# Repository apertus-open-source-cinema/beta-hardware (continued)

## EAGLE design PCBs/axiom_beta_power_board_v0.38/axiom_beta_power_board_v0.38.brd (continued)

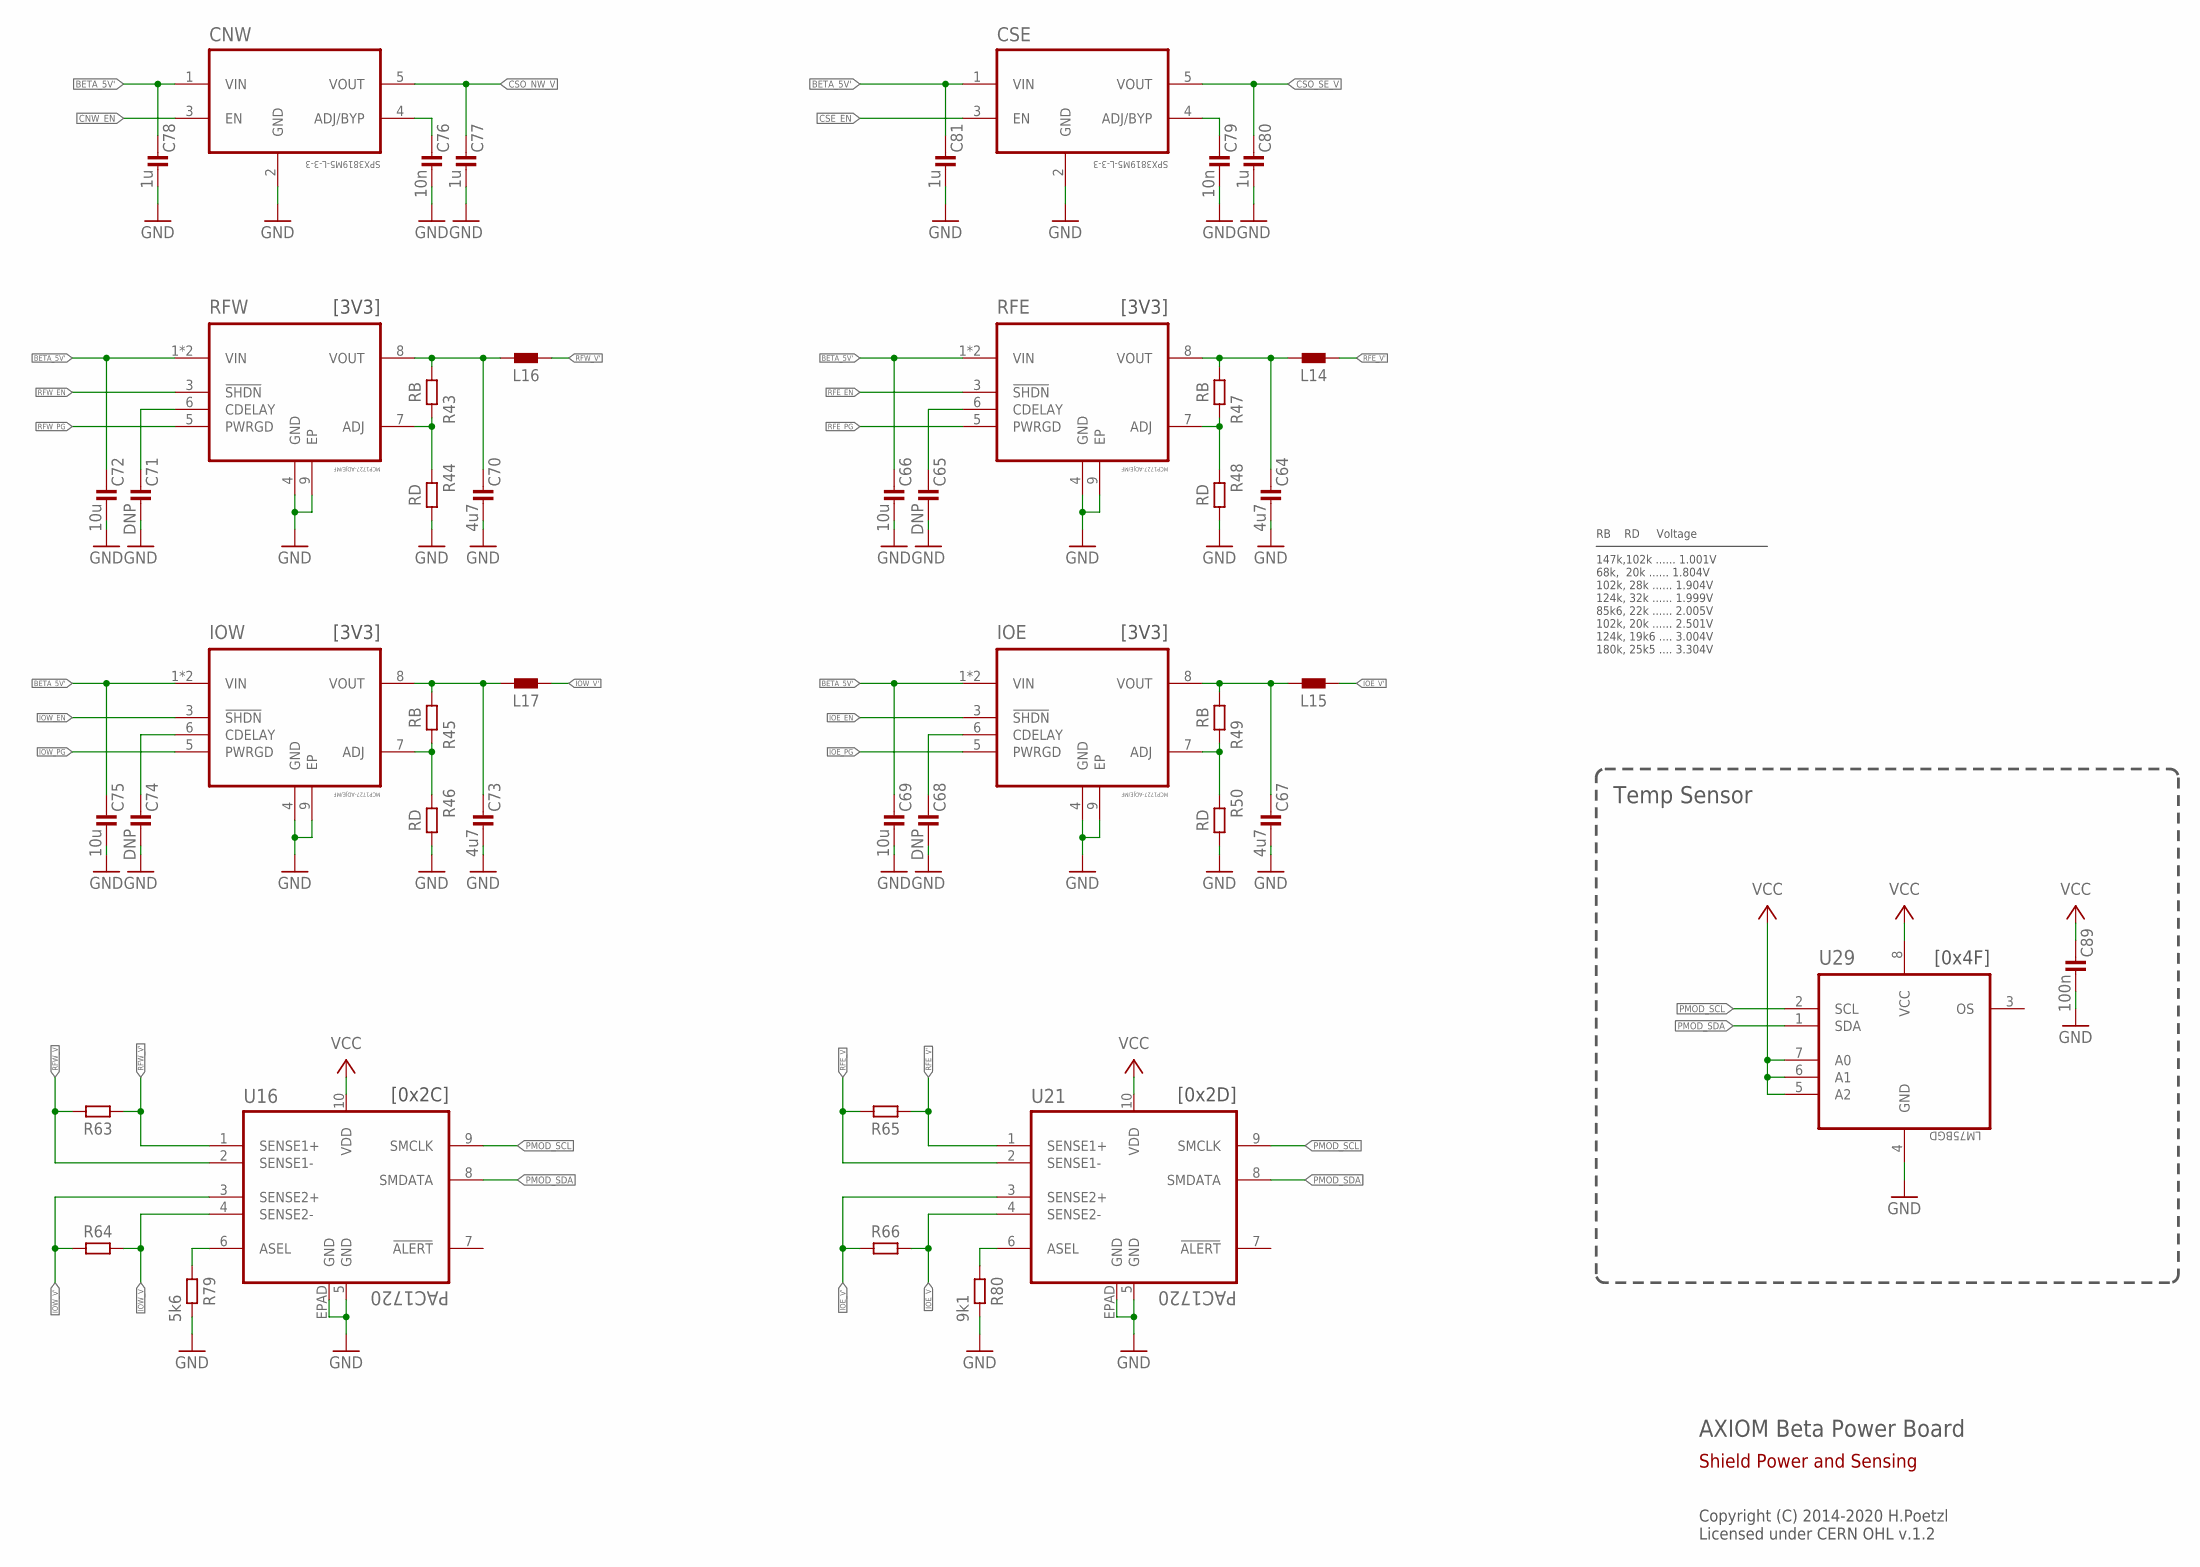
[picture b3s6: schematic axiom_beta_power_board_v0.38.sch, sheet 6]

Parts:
C64, C67, C70, C73: 4u7; 0603-B
C65, C68, C71, C74: DNP; 0402-B
C66, C69, C72, C75: 10u; 0603-B
C76, C79: 10n; 0402-B
C77, C78, C80, C81: 1u; 0402-B
C89: 100n; 0402-B
CNW: SPX3819M5-L-3-3; SOT95P280X145-5N
CSE: SPX3819M5-L-3-3; SOT95P280X145-5N
IOE: MCP1727-ADJE/MF; DFN65P300X300X100-9N
IOW: MCP1727-ADJE/MF; DFN65P300X300X100-9N
L14, L15, L16, L17: L0805-B; 0805-B
R43, R45, R47, R49: RB; 0402-B
R44, R46, R48, R50: RD; 0402-B
R63, R64, R65, R66: R1206-B; 1206-B
R79: 5k6; 0402-B
R80: 9k1; 0402-B
RFE: MCP1727-ADJE/MF; DFN65P300X300X100-9N
RFW: MCP1727-ADJE/MF; DFN65P300X300X100-9N
U16, U21: PAC1720; DFN3X3_10LEAD
U29: LM75BGD; SOT996-2/3

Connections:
BETA_5V': C66.1, C69.1, C72.1, C75.1, C78.1, C81.1, CNW.1 (VIN), CSE.1 (VIN), IOE.1 (VIN), IOE.2 (VIN), IOW.1 (VIN), IOW.2 (VIN), RFE.1 (VIN), RFE.2 (VIN), RFW.1 (VIN), RFW.2 (VIN); also elsewhere on the board
CNW_BYP: C76.1, CNW.4 (ADJ/BYP)
CNW_EN: CNW.3 (EN); also elsewhere on the board
CSE_BYP: C79.1, CSE.4 (ADJ/BYP)
CSE_EN: CSE.3 (EN); also elsewhere on the board
CSO_NW_V: C77.1, CNW.5 (VOUT); also elsewhere on the board
CSO_SE_V: C80.1, CSE.5 (VOUT); also elsewhere on the board
GND: C64.2, C65.2, C66.2, C67.2, C68.2, C69.2, C70.2, C71.2, C72.2, C73.2, C74.2, C75.2, C76.2, C77.2, C78.2, C79.2, C80.2, C81.2, C89.2, CNW.2 (GND), CSE.2 (GND), IOE.4 (GND), IOE.9 (EP), IOW.4 (GND), IOW.9 (EP), R44.2, R46.2, R48.2, R50.2, R79.2, R80.2, RFE.4 (GND), RFE.9 (EP), RFW.4 (GND), RFW.9 (EP), U16.5 (GND), U16.EPAD (GND), U21.5 (GND), U21.EPAD (GND), U29.4 (GND); also elsewhere on the board
IOE_EN: IOE.3 (!SHDN); also elsewhere on the board
IOE_PG: IOE.5 (PWRGD); also elsewhere on the board
IOE_V: R66.2, U21.4 (SENSE2-); also elsewhere on the board
IOE_V': L15.2, R66.1, U21.3 (SENSE2+)
IOW_EN: IOW.3 (!SHDN); also elsewhere on the board
IOW_PG: IOW.5 (PWRGD); also elsewhere on the board
IOW_V: R64.2, U16.4 (SENSE2-); also elsewhere on the board
IOW_V': L17.2, R64.1, U16.3 (SENSE2+)
unnamed: C64.1, L14.1, R47.1, RFE.8 (VOUT)
unnamed: R47.2, R48.1, RFE.7 (ADJ)
unnamed: C65.1, RFE.6 (CDELAY)
unnamed: C67.1, IOE.8 (VOUT), L15.1, R49.1
unnamed: IOE.7 (ADJ), R49.2, R50.1
unnamed: C68.1, IOE.6 (CDELAY)
unnamed: C70.1, L16.1, R43.1, RFW.8 (VOUT)
unnamed: R43.2, R44.1, RFW.7 (ADJ)
unnamed: C71.1, RFW.6 (CDELAY)
unnamed: C73.1, IOW.8 (VOUT), L17.1, R45.1
unnamed: IOW.7 (ADJ), R45.2, R46.1
unnamed: C74.1, IOW.6 (CDELAY)
unnamed: R79.1, U16.6 (ASEL)
unnamed: R80.1, U21.6 (ASEL)
PMOD_SCL: U16.9 (SMCLK), U21.9 (SMCLK), U29.2 (SCL); also elsewhere on the board
PMOD_SDA: U16.8 (SMDATA), U21.8 (SMDATA), U29.1 (SDA); also elsewhere on the board
RFE_EN: RFE.3 (!SHDN); also elsewhere on the board
RFE_PG: RFE.5 (PWRGD); also elsewhere on the board
RFE_V: R65.2, U21.2 (SENSE1-); also elsewhere on the board
RFE_V': L14.2, R65.1, U21.1 (SENSE1+)
RFW_EN: RFW.3 (!SHDN); also elsewhere on the board
RFW_PG: RFW.5 (PWRGD); also elsewhere on the board
RFW_V: R63.2, U16.2 (SENSE1-); also elsewhere on the board
RFW_V': L16.2, R63.1, U16.1 (SENSE1+)
VCC: C89.1, U16.10 (VDD), U21.10 (VDD), U29.5 (A2), U29.6 (A1), U29.7 (A0), U29.8 (VCC); also elsewhere on the board

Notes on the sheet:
AXIOM Beta Power Board
Copyright (C) 2014-2020 H.Poetzl Licensed under CERN OHL v.1.2
Shield Power and Sensing
[0x2C]
[0x2D]
[0x4F]
Temp Sensor
RB RD Voltage 147k,102k ...... 1.001V 68k, 20k ...... 1.804V 102k, 28k ...... 1.904V 124k, 32k ...... 1.999V 85k6, 22k ...... 2.005V 102k, 20k ...... 2.501V 124k, 19k6 .... 3.004V 180k, 25k5 .... 3.304V
[3V3]

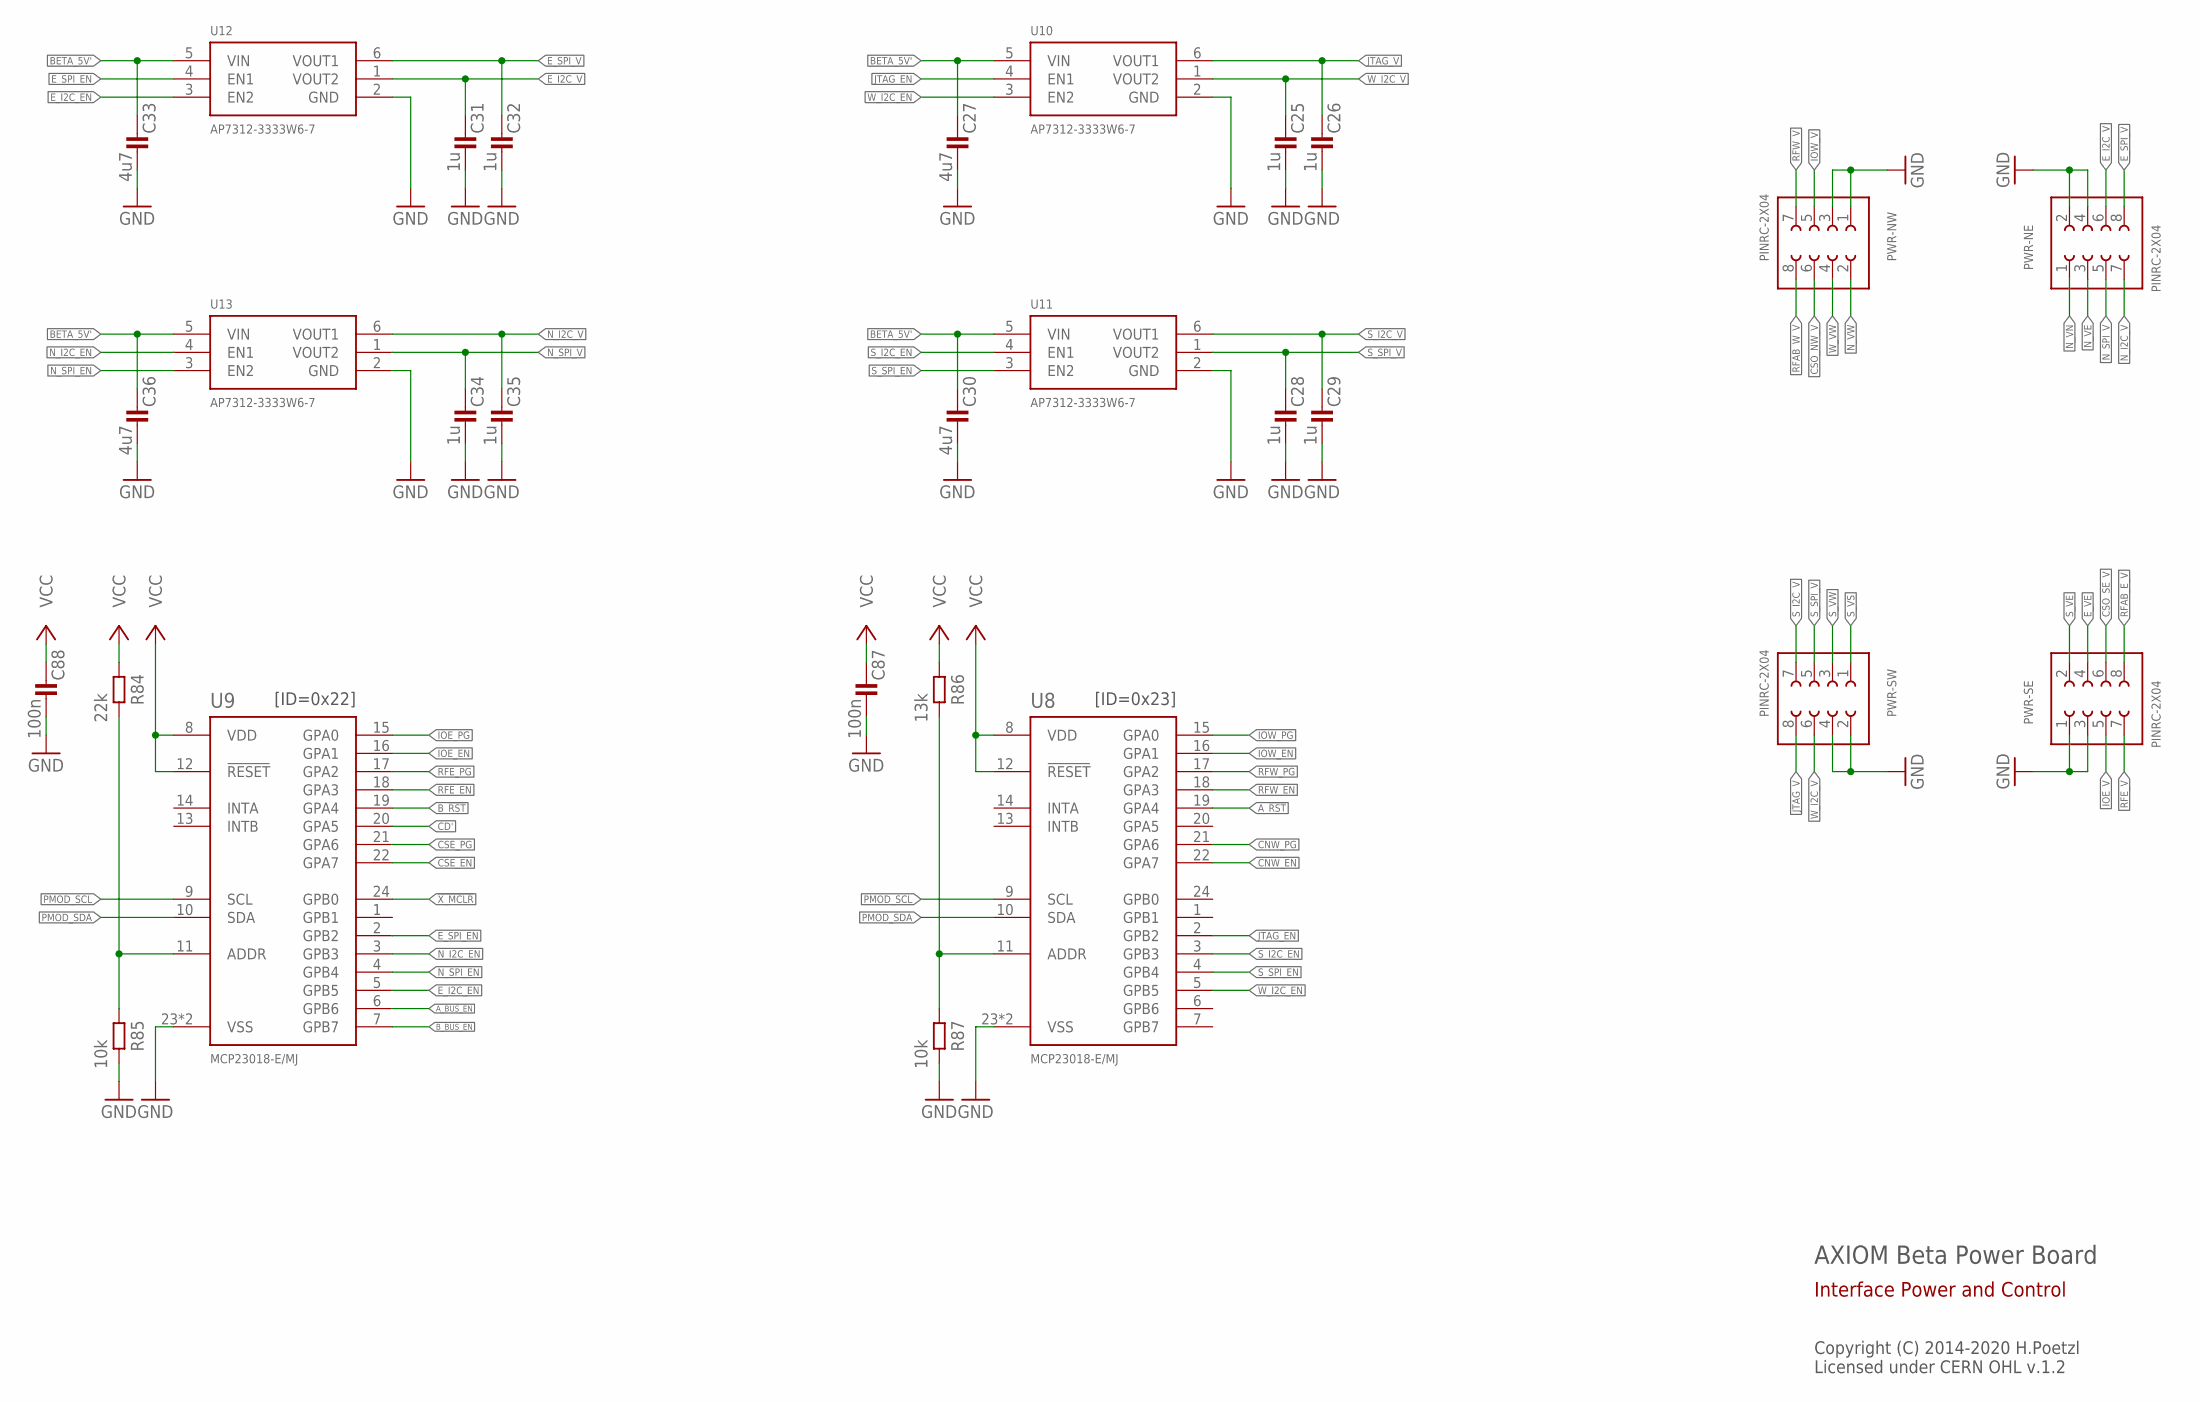
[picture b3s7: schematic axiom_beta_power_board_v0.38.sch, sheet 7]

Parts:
C25, C26, C28, C29, C31, C32, C34, C35: 1u; 0402-B
C27, C30, C33, C36: 4u7; 0603-B
C87, C88: 100n; 0402-B
PWR-NE: PINRC-2X04; R2X04
PWR-NW: PINRC-2X04; R2X04
PWR-SE: PINRC-2X04; R2X04
PWR-SW: PINRC-2X04; R2X04
R84: 22k; 0402-B
R85, R87: 10k; 0402-B
R86: 13k; 0402-B
U8, U9: MCP23018-E/MJ; QFN50P400X400X80-25N
U10, U11, U12, U13: AP7312-3333W6-7; SOT23-6

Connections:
!X_MCLR: U9.24 (GPB0); also elsewhere on the board
A_!RST: U8.19 (GPA4); also elsewhere on the board
A_BUS_EN: U9.6 (GPB6); also elsewhere on the board
BETA_5V': C27.1, C30.1, C33.1, C36.1, U10.5 (VIN), U11.5 (VIN), U12.5 (VIN), U13.5 (VIN); also elsewhere on the board
B_!RST: U9.19 (GPA4); also elsewhere on the board
B_BUS_EN: U9.7 (GPB7); also elsewhere on the board
CD': U9.20 (GPA5); also elsewhere on the board
CNW_EN: U8.22 (GPA7); also elsewhere on the board
CNW_PG: U8.21 (GPA6)
CSE_EN: U9.22 (GPA7); also elsewhere on the board
CSE_PG: U9.21 (GPA6)
CSO_NW_V: PWR-NW.6; also elsewhere on the board
CSO_SE_V: PWR-SE.6; also elsewhere on the board
E_I2C_EN: U9.5 (GPB5), U12.3 (EN2)
E_I2C_V: C31.1, PWR-NE.6, U12.1 (VOUT2)
E_SPI_EN: U9.2 (GPB2), U12.4 (EN1)
E_SPI_V: C32.1, PWR-NE.8, U12.6 (VOUT1)
E_VE: PWR-SE.4; also elsewhere on the board
GND: C25.2, C26.2, C27.2, C28.2, C29.2, C30.2, C31.2, C32.2, C33.2, C34.2, C35.2, C36.2, C87.2, C88.2, PWR-NE.2, PWR-NE.4, PWR-NW.1, PWR-NW.3, PWR-SE.1, PWR-SE.3, PWR-SW.2, PWR-SW.4, R85.2, R87.2, U8.23 (VSS), U8.25 (VSS), U9.23 (VSS), U9.25 (VSS), U10.2 (GND), U11.2 (GND), U12.2 (GND), U13.2 (GND); also elsewhere on the board
IOE_EN: U9.16 (GPA1); also elsewhere on the board
IOE_PG: U9.15 (GPA0); also elsewhere on the board
IOE_V: PWR-SE.5; also elsewhere on the board
IOW_EN: U8.16 (GPA1); also elsewhere on the board
IOW_PG: U8.15 (GPA0); also elsewhere on the board
IOW_V: PWR-NW.5; also elsewhere on the board
JTAG_EN: U8.2 (GPB2), U10.4 (EN1)
JTAG_V: C26.1, PWR-SW.8, U10.6 (VOUT1)
unnamed: R84.2, R85.1, U9.11 (ADDR)
unnamed: R86.2, R87.1, U8.11 (ADDR)
N_I2C_EN: U9.3 (GPB3), U13.4 (EN1)
N_I2C_V: C35.1, PWR-NE.7, U13.6 (VOUT1)
N_SPI_EN: U9.4 (GPB4), U13.3 (EN2)
N_SPI_V: C34.1, PWR-NE.5, U13.1 (VOUT2)
N_VE: PWR-NE.3; also elsewhere on the board
N_VN: PWR-NE.1; also elsewhere on the board
N_VW: PWR-NW.2; also elsewhere on the board
PMOD_SCL: U8.9 (SCL), U9.9 (SCL); also elsewhere on the board
PMOD_SDA: U8.10 (SDA), U9.10 (SDA); also elsewhere on the board
RFAB_E_V: PWR-SE.8
RFAB_W_V: PWR-NW.8
RFE_EN: U9.18 (GPA3); also elsewhere on the board
RFE_PG: U9.17 (GPA2); also elsewhere on the board
RFE_V: PWR-SE.7; also elsewhere on the board
RFW_EN: U8.18 (GPA3); also elsewhere on the board
RFW_PG: U8.17 (GPA2); also elsewhere on the board
RFW_V: PWR-NW.7; also elsewhere on the board
S_I2C_EN: U8.3 (GPB3), U11.4 (EN1)
S_I2C_V: C29.1, PWR-SW.7, U11.6 (VOUT1)
S_SPI_EN: U8.4 (GPB4), U11.3 (EN2)
S_SPI_V: C28.1, PWR-SW.5, U11.1 (VOUT2)
S_VE: PWR-SE.2; also elsewhere on the board
S_VS: PWR-SW.1; also elsewhere on the board
S_VW: PWR-SW.3; also elsewhere on the board
VCC: C87.1, C88.1, R84.1, R86.1, U8.8 (VDD), U8.12 (!RESET), U9.8 (VDD), U9.12 (!RESET); also elsewhere on the board
W_I2C_EN: U8.5 (GPB5), U10.3 (EN2)
W_I2C_V: C25.1, PWR-SW.6, U10.1 (VOUT2)
W_VW: PWR-NW.4; also elsewhere on the board

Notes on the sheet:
AXIOM Beta Power Board
Copyright (C) 2014-2020 H.Poetzl Licensed under CERN OHL v.1.2
Interface Power and Control
[ID=0x22]
[ID=0x23]

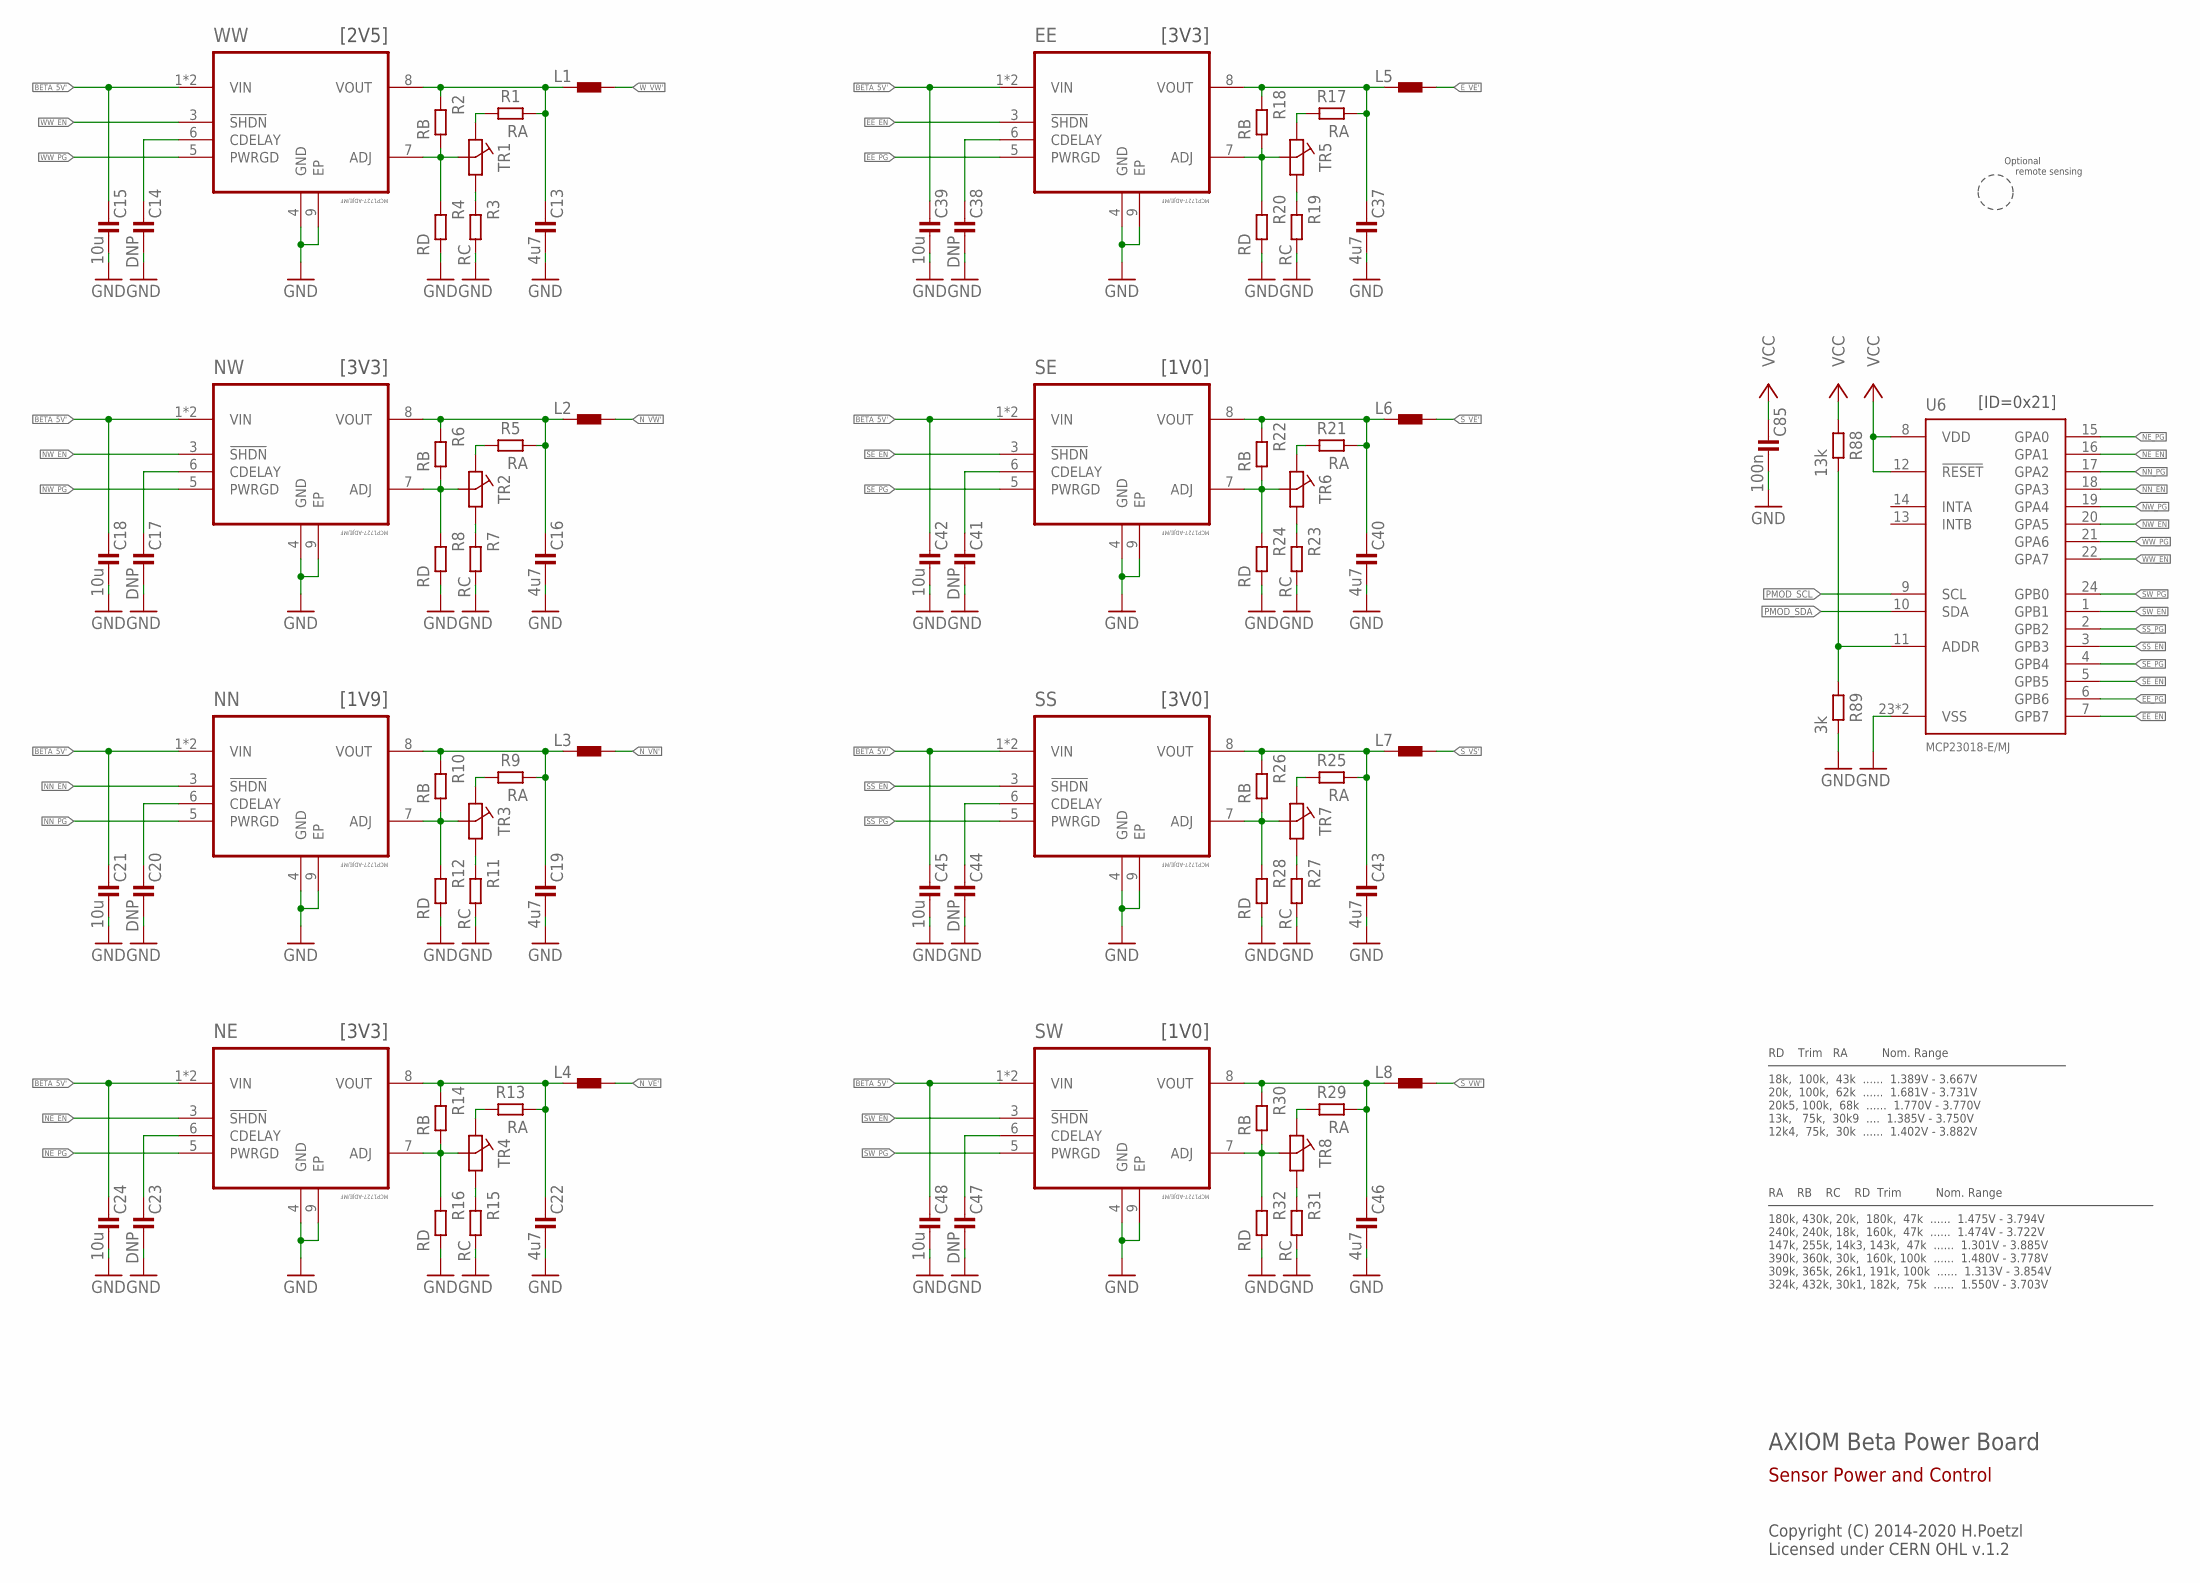
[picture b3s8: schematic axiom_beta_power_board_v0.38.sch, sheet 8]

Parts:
C13, C16, C19, C22, C37, C40, C43, C46: 4u7; 0603-B
C14, C17, C20, C23, C38, C41, C44, C47: DNP; 0402-B
C15, C18, C21, C24, C39, C42, C45, C48: 10u; 0603-B
C85: 100n; 0402-B
EE: MCP1727-ADJE/MF; DFN65P300X300X100-9N
L1, L2, L3, L4, L5, L6, L7, L8: L0805-B; 0805-B
NE: MCP1727-ADJE/MF; DFN65P300X300X100-9N
NN: MCP1727-ADJE/MF; DFN65P300X300X100-9N
NW: MCP1727-ADJE/MF; DFN65P300X300X100-9N
R1, R5, R9, R13, R17, R21, R25, R29: RA; 0402-B
R2, R6, R10, R14, R18, R22, R26, R30: RB; 0402-B
R3, R7, R11, R15, R19, R23, R27, R31: RC; 0402-B
R4, R8, R12, R16, R20, R24, R28, R32: RD; 0402-B
R88: 13k; 0402-B
R89: 3k; 0402-B
SE: MCP1727-ADJE/MF; DFN65P300X300X100-9N
SS: MCP1727-ADJE/MF; DFN65P300X300X100-9N
SW: MCP1727-ADJE/MF; DFN65P300X300X100-9N
TR1, TR2, TR3, TR4, TR5, TR6, TR7, TR8: PVZ2A; TRIM-PVZ2A
U6: MCP23018-E/MJ; QFN50P400X400X80-25N
WW: MCP1727-ADJE/MF; DFN65P300X300X100-9N

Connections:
BETA_5V': C15.1, C18.1, C21.1, C24.1, C39.1, C42.1, C45.1, C48.1, EE.1 (VIN), EE.2 (VIN), NE.1 (VIN), NE.2 (VIN), NN.1 (VIN), NN.2 (VIN), NW.1 (VIN), NW.2 (VIN), SE.1 (VIN), SE.2 (VIN), SS.1 (VIN), SS.2 (VIN), SW.1 (VIN), SW.2 (VIN), WW.1 (VIN), WW.2 (VIN); also elsewhere on the board
EE_EN: EE.3 (!SHDN), U6.7 (GPB7)
EE_PG: EE.5 (PWRGD), U6.6 (GPB6)
E_VE': L5.2; also elsewhere on the board
GND: C13.2, C14.2, C15.2, C16.2, C17.2, C18.2, C19.2, C20.2, C21.2, C22.2, C23.2, C24.2, C37.2, C38.2, C39.2, C40.2, C41.2, C42.2, C43.2, C44.2, C45.2, C46.2, C47.2, C48.2, C85.2, EE.4 (GND), EE.9 (EP), NE.4 (GND), NE.9 (EP), NN.4 (GND), NN.9 (EP), NW.4 (GND), NW.9 (EP), R3.2, R4.2, R7.2, R8.2, R11.2, R12.2, R15.2, R16.2, R19.2, R20.2, R23.2, R24.2, R27.2, R28.2, R31.2, R32.2, R89.2, SE.4 (GND), SE.9 (EP), SS.4 (GND), SS.9 (EP), SW.4 (GND), SW.9 (EP), U6.23 (VSS), U6.25 (VSS), WW.4 (GND), WW.9 (EP); also elsewhere on the board
unnamed: C13.1, L1.1, R1.2, R2.1, WW.8 (VOUT)
unnamed: R2.2, R4.1, TR1.2 (B), WW.7 (ADJ)
unnamed: R3.1, TR1.1 (A)
unnamed: C14.1, WW.6 (CDELAY)
unnamed: R1.1, TR1.3 (C)
unnamed: C16.1, L2.1, NW.8 (VOUT), R5.2, R6.1
unnamed: NW.7 (ADJ), R6.2, R8.1, TR2.2 (B)
unnamed: R7.1, TR2.1 (A)
unnamed: C17.1, NW.6 (CDELAY)
unnamed: C19.1, L3.1, NN.8 (VOUT), R9.2, R10.1
unnamed: NN.7 (ADJ), R10.2, R12.1, TR3.2 (B)
unnamed: R5.1, TR2.3 (C)
unnamed: C20.1, NN.6 (CDELAY)
unnamed: C22.1, L4.1, NE.8 (VOUT), R13.2, R14.1
unnamed: NE.7 (ADJ), R14.2, R16.1, TR4.2 (B)
unnamed: R11.1, TR3.1 (A)
unnamed: C23.1, NE.6 (CDELAY)
unnamed: C37.1, EE.8 (VOUT), L5.1, R17.2, R18.1
unnamed: EE.7 (ADJ), R18.2, R20.1, TR5.2 (B)
unnamed: R9.1, TR3.3 (C)
unnamed: C38.1, EE.6 (CDELAY)
unnamed: R15.1, TR4.1 (A)
unnamed: C40.1, L6.1, R21.2, R22.1, SE.8 (VOUT)
unnamed: R22.2, R24.1, SE.7 (ADJ), TR6.2 (B)
unnamed: R13.1, TR4.3 (C)
unnamed: C41.1, SE.6 (CDELAY)
unnamed: R19.1, TR5.1 (A)
unnamed: C43.1, L7.1, R25.2, R26.1, SS.8 (VOUT)
unnamed: R26.2, R28.1, SS.7 (ADJ), TR7.2 (B)
unnamed: R17.1, TR5.3 (C)
unnamed: C44.1, SS.6 (CDELAY)
unnamed: R23.1, TR6.1 (A)
unnamed: C46.1, L8.1, R29.2, R30.1, SW.8 (VOUT)
unnamed: R30.2, R32.1, SW.7 (ADJ), TR8.2 (B)
unnamed: R21.1, TR6.3 (C)
unnamed: C47.1, SW.6 (CDELAY)
unnamed: R27.1, TR7.1 (A)
unnamed: R25.1, TR7.3 (C)
unnamed: R31.1, TR8.1 (A)
unnamed: R29.1, TR8.3 (C)
unnamed: R88.2, R89.1, U6.11 (ADDR)
NE_EN: NE.3 (!SHDN), U6.16 (GPA1)
NE_PG: NE.5 (PWRGD), U6.15 (GPA0)
NN_EN: NN.3 (!SHDN), U6.18 (GPA3)
NN_PG: NN.5 (PWRGD), U6.17 (GPA2)
NW_EN: NW.3 (!SHDN), U6.20 (GPA5)
NW_PG: NW.5 (PWRGD), U6.19 (GPA4)
N_VE': L4.2; also elsewhere on the board
N_VN': L3.2; also elsewhere on the board
N_VW': L2.2; also elsewhere on the board
PMOD_SCL: U6.9 (SCL); also elsewhere on the board
PMOD_SDA: U6.10 (SDA); also elsewhere on the board
SE_EN: SE.3 (!SHDN), U6.5 (GPB5)
SE_PG: SE.5 (PWRGD), U6.4 (GPB4)
SS_EN: SS.3 (!SHDN), U6.3 (GPB3)
SS_PG: SS.5 (PWRGD), U6.2 (GPB2)
SW_EN: SW.3 (!SHDN), U6.1 (GPB1)
SW_PG: SW.5 (PWRGD), U6.24 (GPB0)
S_VE': L6.2; also elsewhere on the board
S_VS': L7.2; also elsewhere on the board
S_VW': L8.2; also elsewhere on the board
VCC: C85.1, R88.1, U6.8 (VDD), U6.12 (!RESET); also elsewhere on the board
WW_EN: U6.22 (GPA7), WW.3 (!SHDN)
WW_PG: U6.21 (GPA6), WW.5 (PWRGD)
W_VW': L1.2; also elsewhere on the board

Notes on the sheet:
AXIOM Beta Power Board
Copyright (C) 2014-2020 H.Poetzl Licensed under CERN OHL v.1.2
Sensor Power and Control
[ID=0x21]
RD Trim RA Nom. Range 18k, 100k, 43k ...... 1.389V - 3.667V 20k, 100k, 62k ...... 1.681V - 3.731V 20k5, 100k, 68k ...... 1.770V - 3.770V 13k, 75k, 30k9 .... 1.385V - 3.750V 12k4, 75k, 30k ...... 1.402V - 3.882V
Optional remote sensing
RA RB RC RD Trim Nom. Range 180k, 430k, 20k, 180k, 47k ...... 1.475V - 3.794V 240k, 240k, 18k, 160k, 47k ...... 1.474V - 3.722V 147k, 255k, 14k3, 143k, 47k ...... 1.301V - 3.885V 390k, 360k, 30k, 160k, 100k ...... 1.480V - 3.778V 309k, 365k, 26k1, 191k, 100k ...... 1.313V - 3.854V 324k, 432k, 30k1,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
[2V5]
[3V3]
[1V9]
[1V0]
[3V0]

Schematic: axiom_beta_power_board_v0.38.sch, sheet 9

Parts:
R51, R52, R53, R54, R55, R56, R57, R58, R59, R60, R61, R62: R1206-B; 1206-B
R73: 750R; 0402-B
R74: 1k27; 0402-B
R75: 430R; 0402-B
R76: 0R; 0402-B
R77: 100R; 0402-B
R78: 560R; 0402-B
U17, U18, U19, U20, U23, U24: PAC1720; DFN3X3_10LEAD

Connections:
E_VE: R57.2, U19.2 (SENSE1-); also elsewhere on the board
E_VE': R57.1, U19.1 (SENSE1+); also elsewhere on the board
GND: R73.2, R74.2, R75.2, R76.2, R77.2, R78.2, U17.5 (GND), U17.EPAD (GND), U18.5 (GND), U18.EPAD (GND), U19.5 (GND), U19.EPAD (GND), U20.5 (GND), U20.EPAD (GND), U23.5 (GND), U23.EPAD (GND), U24.5 (GND), U24.EPAD (GND); also elsewhere on the board
unnamed: R73.1, U18.6 (ASEL)
unnamed: R75.1, U24.6 (ASEL)
unnamed: R78.1, U23.6 (ASEL)
unnamed: R74.1, U20.6 (ASEL)
unnamed: R76.1, U19.6 (ASEL)
unnamed: R77.1, U17.6 (ASEL)
N_VE: R54.2, U20.4 (SENSE2-); also elsewhere on the board
N_VE': R54.1, U20.3 (SENSE2+); also elsewhere on the board
N_VN: R53.2, U20.2 (SENSE1-); also elsewhere on the board
N_VN': R53.1, U20.1 (SENSE1+); also elsewhere on the board
N_VW: R52.2, U18.4 (SENSE2-); also elsewhere on the board
N_VW': R52.1, U18.3 (SENSE2+); also elsewhere on the board
PCIE_VCCIO: R61.2, U23.2 (SENSE1-)
PMOD_SCL: U17.9 (SMCLK), U18.9 (SMCLK), U19.9 (SMCLK), U20.9 (SMCLK), U23.9 (SMCLK), U24.9 (SMCLK); also elsewhere on the board
PMOD_SDA: U17.8 (SMDATA), U18.8 (SMDATA), U19.8 (SMDATA), U20.8 (SMDATA), U23.8 (SMDATA), U24.8 (SMDATA); also elsewhere on the board
S_VE: R58.2, U19.4 (SENSE2-); also elsewhere on the board
S_VE': R58.1, U19.3 (SENSE2+); also elsewhere on the board
S_VS: R59.2, U17.2 (SENSE1-); also elsewhere on the board
S_VS': R59.1, U17.1 (SENSE1+); also elsewhere on the board
S_VW: R60.2, U17.4 (SENSE2-); also elsewhere on the board
S_VW': R60.1, U17.3 (SENSE2+); also elsewhere on the board
VCC: U17.10 (VDD), U18.10 (VDD), U19.10 (VDD), U20.10 (VDD), U23.10 (VDD), U24.10 (VDD); also elsewhere on the board
VCCIO: R55.1, R56.1, R61.1, R62.1, U23.1 (SENSE1+), U23.3 (SENSE2+), U24.1 (SENSE1+), U24.3 (SENSE2+); also elsewhere on the board
VCCO_13: R56.2, U24.4 (SENSE2-); also elsewhere on the board
VCCO_34: R62.2, U23.4 (SENSE2-); also elsewhere on the board
VCCO_35: R55.2, U24.2 (SENSE1-); also elsewhere on the board
W_VW: R51.2, U18.2 (SENSE1-); also elsewhere on the board
W_VW': R51.1, U18.1 (SENSE1+); also elsewhere on the board

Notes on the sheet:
AXIOM Beta Power Board
Copyright (C) 2014-2020 H.Poetzl Licensed under CERN OHL v.1.2
Sensor Power Sensing
[0x48]
[0x49]
[0x4B]
[0x4D]
[0x4A]
[0x4C]

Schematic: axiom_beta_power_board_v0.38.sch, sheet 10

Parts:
C49, C52, C55, C58, C61: 4u7; 0603-B
C50, C53, C56, C59, C62: DNP; 0402-B
C51, C54, C57, C60, C63: 10u; 0603-B
C86: 100n; 0402-B
L9, L10, L11, L12, L13: L0805-A; 0805-A
MCN: MCP1727-ADJE/MF; DFN65P300X300X100-9N
MCS: MCP1727-ADJE/MF; DFN65P300X300X100-9N
MXN: MCP1727-ADJE/MF; DFN65P300X300X100-9N
MXS: MCP1727-ADJE/MF; DFN65P300X300X100-9N
R33, R35, R39, R41: RB; 0402-B
R34, R36, R40, R42: RD; 0402-B
R37: 102k; 0402-B
R38: 20k; 0402-B
R67, R68, R69, R70, R71, R72: R1206-B; 1206-B
R81: 2k0; 0402-B
R82: 1k6; 0402-B
R83: 2k7; 0402-B
R90: 15k; 0402-B
R91: 1k; 0402-B
U7: MCP23018-E/MJ; QFN50P400X400X80-25N
U14, U15, U22: PAC1720; DFN3X3_10LEAD
VIO: MCP1727-ADJE/MF; DFN65P300X300X100-9N

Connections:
BETA_5V: R70.1, U22.3 (SENSE2+); also elsewhere on the board
BETA_5V': C51.1, C54.1, C57.1, C60.1, C63.1, MCN.1 (VIN), MCN.2 (VIN), MCS.1 (VIN), MCS.2 (VIN), MXN.1 (VIN), MXN.2 (VIN), MXS.1 (VIN), MXS.2 (VIN), R70.2, U22.4 (SENSE2-), VIO.1 (VIN), VIO.2 (VIN); also elsewhere on the board
CSO_NE_V: R67.2, U14.2 (SENSE1-); also elsewhere on the board
CSO_N_V': L12.2, R67.1, U14.1 (SENSE1+)
CSO_SW_V: R71.2, U15.2 (SENSE1-); also elsewhere on the board
CSO_S_V': L10.2, R71.1, U15.1 (SENSE1+)
GND: C49.2, C50.2, C51.2, C52.2, C53.2, C54.2, C55.2, C56.2, C57.2, C58.2, C59.2, C60.2, C61.2, C62.2, C63.2, C86.2, MCN.4 (GND), MCN.9 (EP), MCS.4 (GND), MCS.9 (EP), MXN.4 (GND), MXN.9 (EP), MXS.4 (GND), MXS.9 (EP), R34.2, R36.2, R38.2, R40.2, R42.2, R81.2, R82.2, R83.2, R91.2, U7.23 (VSS), U7.25 (VSS), U14.5 (GND), U14.EPAD (GND), U15.5 (GND), U15.EPAD (GND), U22.5 (GND), U22.EPAD (GND), VIO.4 (GND), VIO.9 (EP); also elsewhere on the board
MCN_EN: MCN.3 (!SHDN), U7.18 (GPA3)
MCN_PG: MCN.5 (PWRGD), U7.17 (GPA2)
MCS_EN: MCS.3 (!SHDN), U7.22 (GPA7)
MCS_PG: MCS.5 (PWRGD), U7.21 (GPA6)
MXN_EN: MXN.3 (!SHDN), U7.16 (GPA1)
MXN_PG: MXN.5 (PWRGD), U7.15 (GPA0)
MXS_EN: MXS.3 (!SHDN), U7.1 (GPB1)
MXS_PG: MXS.5 (PWRGD), U7.24 (GPB0)
unnamed: C49.1, L9.1, MXS.8 (VOUT), R41.1
unnamed: MXS.7 (ADJ), R41.2, R42.1
unnamed: C50.1, MXS.6 (CDELAY)
unnamed: R81.1, U14.6 (ASEL)
unnamed: R83.1, U15.6 (ASEL)
unnamed: C52.1, L10.1, MCS.8 (VOUT), R39.1
unnamed: MCS.7 (ADJ), R39.2, R40.1
unnamed: C53.1, MCS.6 (CDELAY)
unnamed: R82.1, U22.6 (ASEL)
unnamed: C55.1, L11.1, R37.1, VIO.8 (VOUT)
unnamed: R37.2, R38.1, VIO.7 (ADJ)
unnamed: C56.1, VIO.6 (CDELAY)
unnamed: C58.1, L12.1, MCN.8 (VOUT), R35.1
unnamed: MCN.7 (ADJ), R35.2, R36.1
unnamed: C59.1, MCN.6 (CDELAY)
unnamed: C61.1, L13.1, MXN.8 (VOUT), R33.1
unnamed: MXN.7 (ADJ), R33.2, R34.1
unnamed: C62.1, MXN.6 (CDELAY)
unnamed: R90.2, R91.1, U7.11 (ADDR)
PCIE_N_V: R68.2, U14.4 (SENSE2-); also elsewhere on the board
PCIE_N_V': L13.2, R68.1, U14.3 (SENSE2+)
PCIE_S_V: R72.2, U15.4 (SENSE2-); also elsewhere on the board
PCIE_S_V': L9.2, R72.1, U15.3 (SENSE2+)
PMOD_SCL: U7.9 (SCL), U14.9 (SMCLK), U15.9 (SMCLK), U22.9 (SMCLK); also elsewhere on the board
PMOD_SDA: U7.10 (SDA), U14.8 (SMDATA), U15.8 (SMDATA), U22.8 (SMDATA); also elsewhere on the board
VCC: C86.1, R90.1, U7.8 (VDD), U7.12 (!RESET), U14.10 (VDD), U15.10 (VDD), U22.10 (VDD); also elsewhere on the board
VCCIO: L11.2; also elsewhere on the board
VIO_EN: U7.20 (GPA5), VIO.3 (!SHDN)
VIO_PG: U7.19 (GPA4), VIO.5 (PWRGD)
ZED_5V: R69.1, U22.1 (SENSE1+); also elsewhere on the board
ZED_5V': R69.2, U22.2 (SENSE1-); also elsewhere on the board

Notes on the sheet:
AXIOM Beta Power Board
Copyright (C) 2014-2020 H.Poetzl Licensed under CERN OHL v.1.2
Power, Control and Sensing
[ID=0x20]
[0x29]
[0x28]
[0x2A]
[3V3]
[2V5]

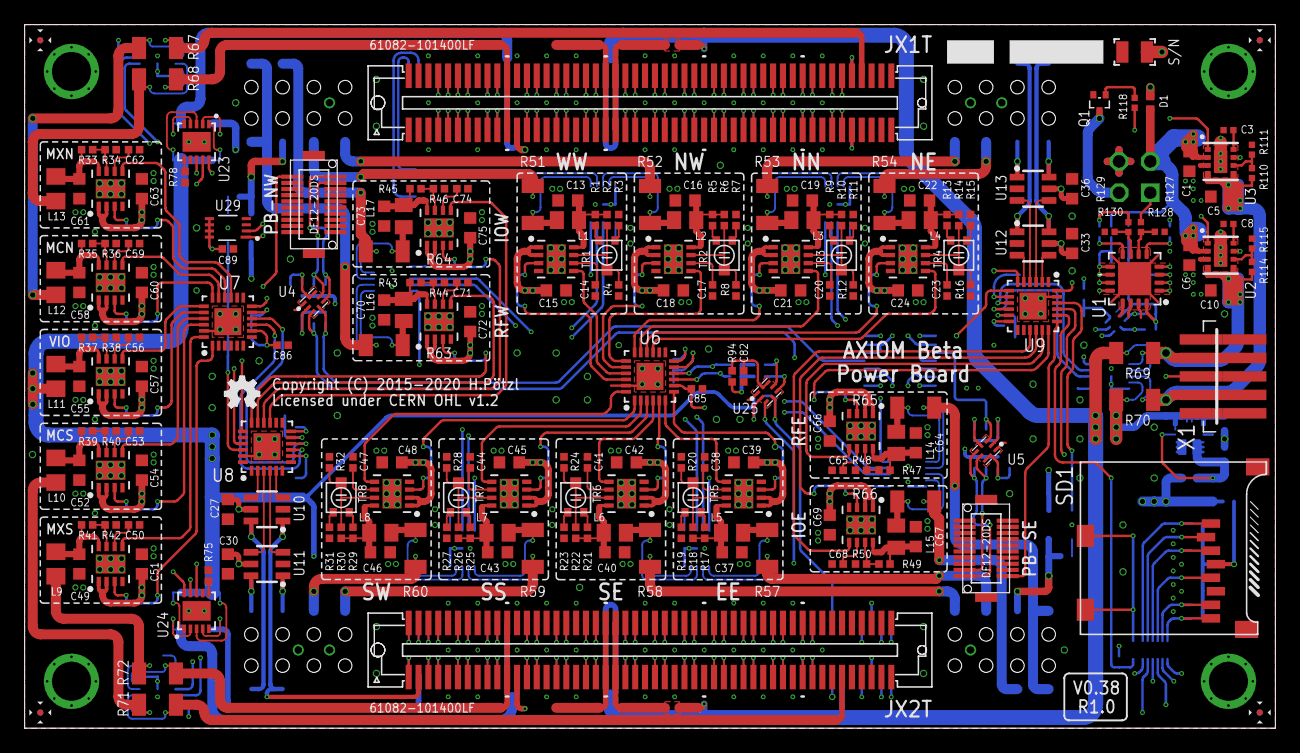
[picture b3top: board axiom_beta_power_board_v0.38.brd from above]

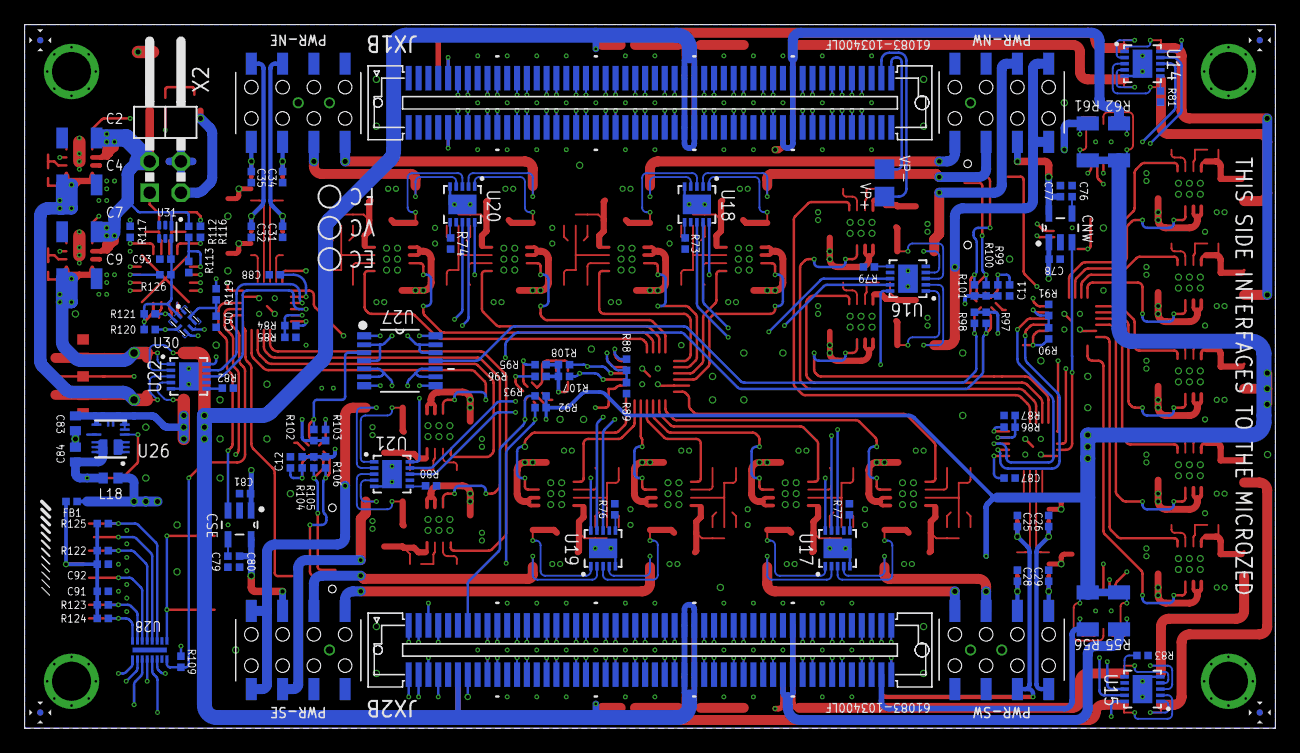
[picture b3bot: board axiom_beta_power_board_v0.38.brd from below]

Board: 4 copper layers, 101.6 x 57.1 mm, 329 parts (110 on the bottom side), 360 nets.

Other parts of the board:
LOGO1: OSHW_LOGO_FILLX0100-NT; OSHW_FILLX100_NOTEXT
